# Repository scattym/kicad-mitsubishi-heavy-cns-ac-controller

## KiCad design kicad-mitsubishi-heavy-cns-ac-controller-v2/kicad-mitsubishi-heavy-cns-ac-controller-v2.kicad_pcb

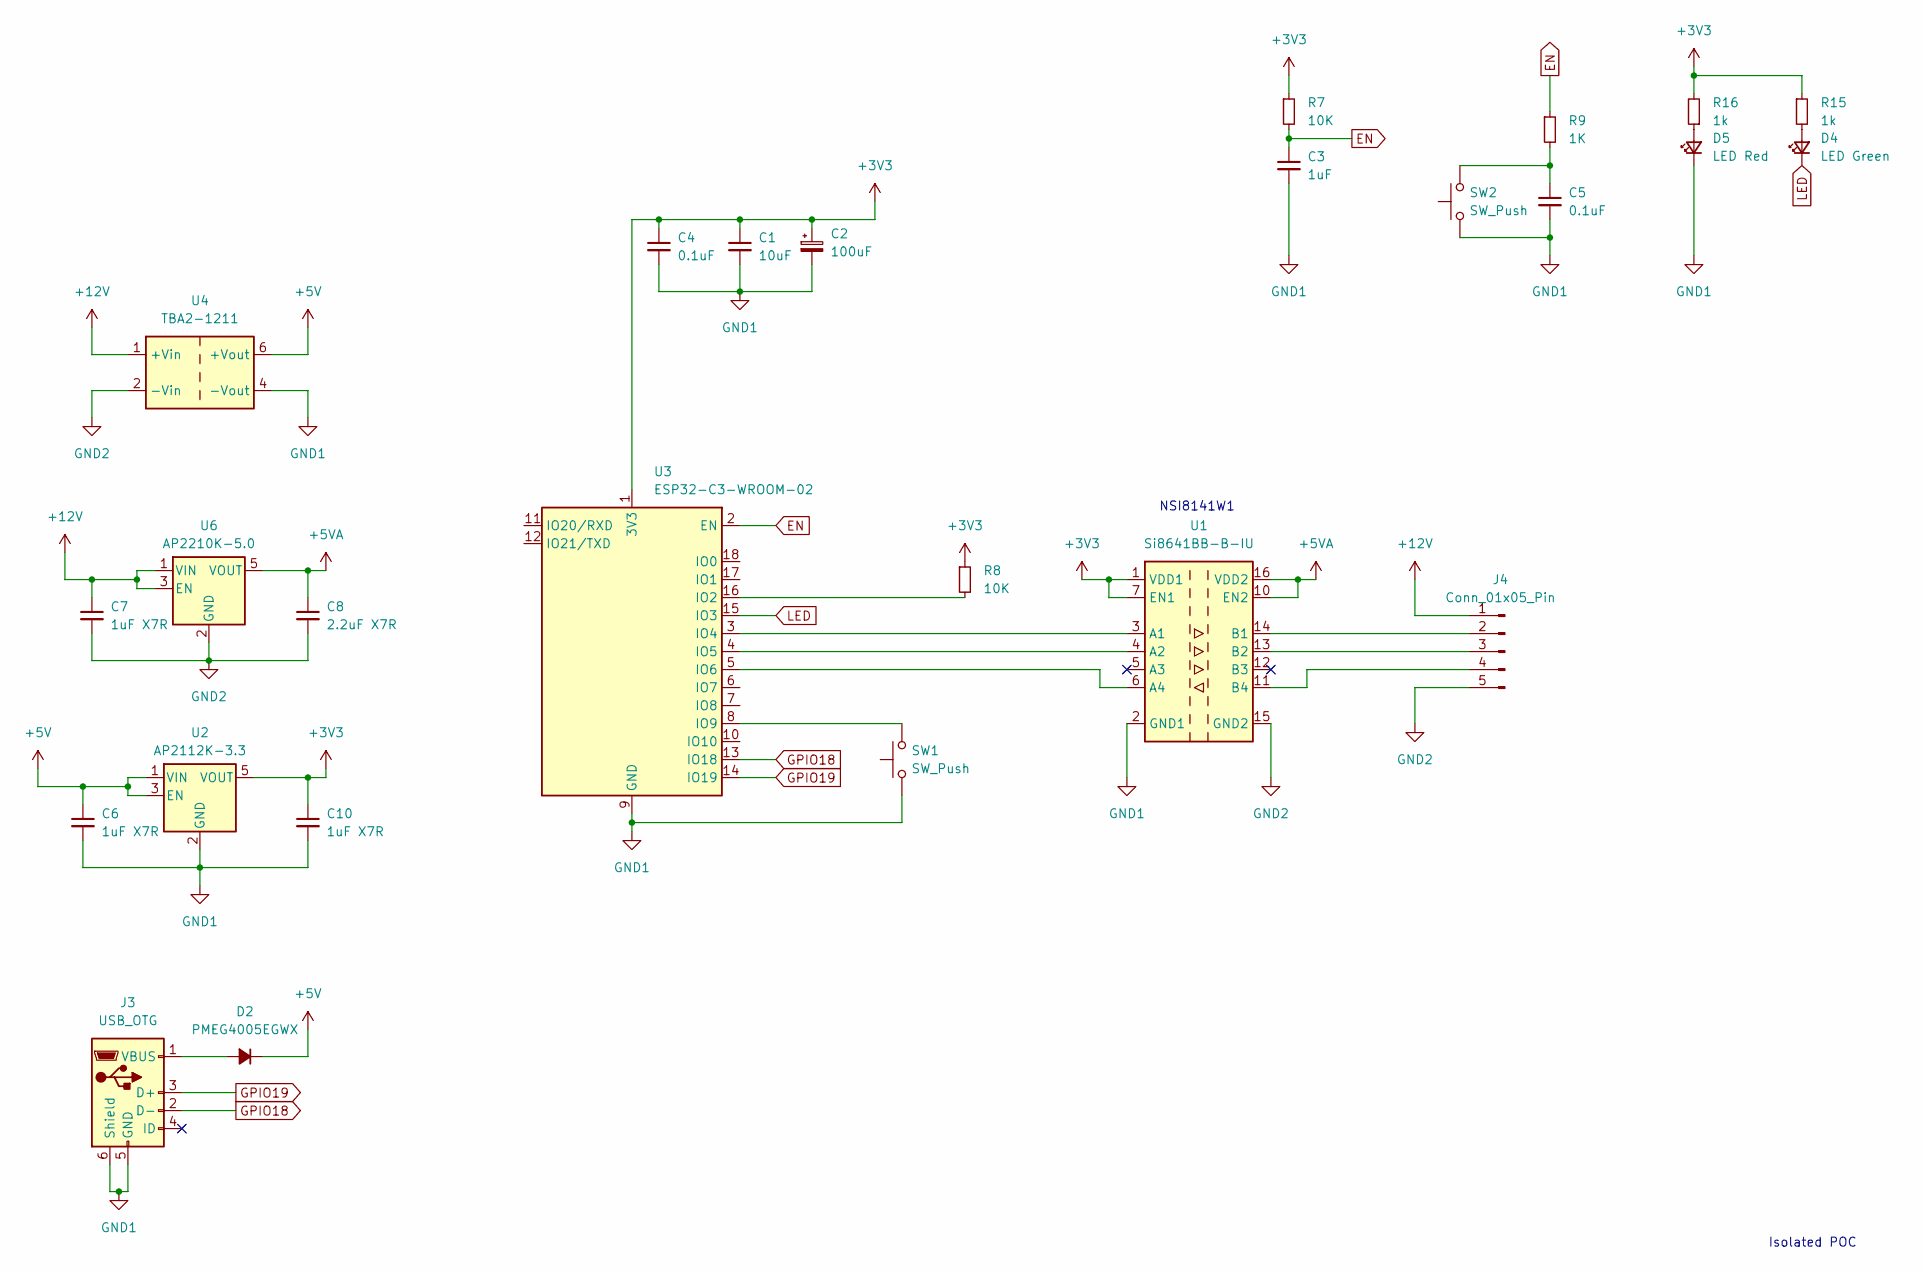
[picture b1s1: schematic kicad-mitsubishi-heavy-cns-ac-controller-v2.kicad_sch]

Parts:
C1: 10uF; C_0603_1608Metric
C2: 100uF; CP_EIA-3528-12_Kemet-T_HandSolder
C3: 1uF; C_0603_1608Metric
C4, C5: 0.1uF; C_0603_1608Metric
C6, C7, C10: 1uF X7R; C_0603_1608Metric
C8: 2.2uF X7R; C_0603_1608Metric
D2: PMEG4005EGWX; D_SOD-123
D4: LED Green; LED_0603_1608Metric
D5: LED Red; LED_0603_1608Metric
J3: USB_OTG; USB_Micro-B_Molex-105017-0001
J4: Conn_01x05_Pin; PinHeader_1x05_P2.54mm_Vertical
R7, R8: 10K; R_0603_1608Metric
R9: 1K; R_0603_1608Metric
R15, R16: 1k; R_0603_1608Metric
SW1, SW2: SW_Push; SW_SPST_CK_RS282G05A3
U1: Si8641BB-B-IU; QSOP-16_3.9x4.9mm_P0.635mm
U2: AP2112K-3.3; SOT-23-5
U3: ESP32-C3-WROOM-02
U4: TBA2-1211; Converter_DCDC_TRACO_TBA2-xxxx_Single_THT
U6: AP2210K-5.0; SOT-23-5

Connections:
+3V3: C1.1, C2.1, C4.1, C10.1, R7.1, R8.1, R15.1, R16.2, U1.1 (VDD1), U1.7 (EN1), U2.5 (VOUT), U3.1 (3V3)
+5V: C6.1, D2.1 (K), U2.1 (VIN), U2.3 (EN), U4.6 (+Vout)
+5VA: C8.1, U1.10 (EN2), U1.16 (VDD2), U6.5 (VOUT)
+12V: C7.1, J4.1, U4.1 (+Vin), U6.1 (VIN), U6.3 (EN)
EN: C3.1, R7.2, R9.1, U3.2 (EN)
GND1: C1.2, C2.2, C3.2, C4.2, C5.2, C6.2, C10.2, D5.1 (K), J3.5 (GND), J3.6 (Shield), SW1.1, SW2.1, U1.2 (GND1), U1.8 (GND1), U2.2 (GND), U3.9 (GND), U3.19 (GND), U4.4 (-Vout)
GND2: C7.2, C8.2, J4.5, U1.9 (GND2), U1.15 (GND2), U4.2 (-Vin), U6.2 (GND)
GPIO18: J3.2 (D-), U3.13 (IO18)
GPIO19: J3.3 (D+), U3.14 (IO19)
LED: D4.1 (K), U3.15 (IO3)
unnamed: C5.1, R9.2, SW2.2
unnamed: D2.2 (A), J3.1 (VBUS)
unnamed: D4.2 (A), R15.2
unnamed: D5.2 (A), R16.1
unnamed: J4.2, U1.14 (B1)
unnamed: J4.3, U1.13 (B2)
unnamed: J4.4, U1.11 (B4)
unnamed: U1.3 (A1), U3.3 (IO4)
unnamed: U1.4 (A2), U3.4 (IO5)
unnamed: U1.6 (A4), U3.5 (IO6)
unnamed: R8.2, U3.16 (IO2)
unnamed: SW1.2, U3.8 (IO9)

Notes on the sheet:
NSI8141W1
Isolated POC

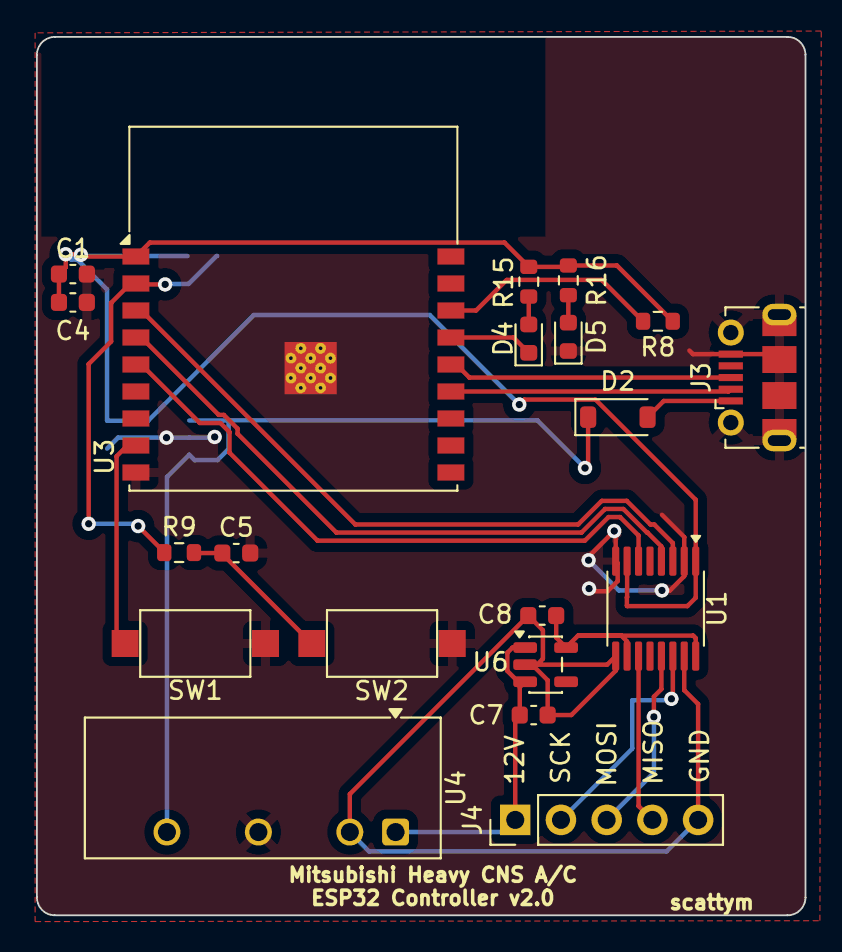
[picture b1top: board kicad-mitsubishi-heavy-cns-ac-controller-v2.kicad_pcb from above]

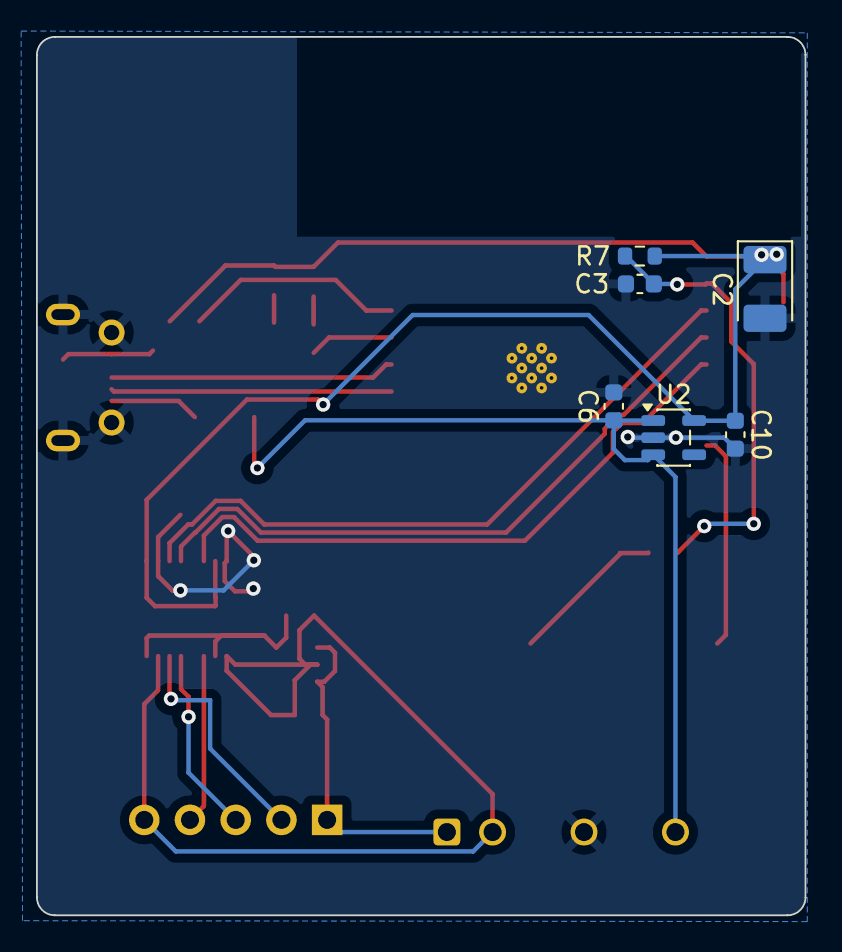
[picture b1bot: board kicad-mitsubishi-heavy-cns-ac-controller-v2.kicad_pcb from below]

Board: 2 copper layers, 42.7 x 48.8 mm, 26 parts (6 on the bottom side), 22 nets.
